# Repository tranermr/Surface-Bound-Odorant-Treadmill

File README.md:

# Surface-Bound-Odorant-Treadmill

One of the important subsets of odors sources used in olfactory navigation is surface-bound sources, which can broadly take the form of point sources or trails. Here, we present an automated treadmill design capable of dynamically printing odor trails of arbitrary lengths and configurations, and with closed-loop control of speed based on the animal’s movement. This design is presented and the utility demonstrated in a corresponding paper studying surface-bound odor trail interactions in locusts (in submission).The uploaded design incorporates some improvements not reflected in the version used in the published paper (i.e. the modification of some components to reduce paper jams, and quality of life improvements). The design is provided in four directories, containing the mechanical components, the electrical component design, and the software and firmware for operation.

The treadmill is designed to enable long-duration interactions with surface-bound odor trails of arbitrary length. Below you can see a video of a locust engaged in a bout of trail following with an odor trail, where the treadmill advances once the locust approaches the front of the behavior chamber, revealing more trail for the locust to interact wtih.

The treadmill is comprised of a series of modules sequentially connected and mounted on an 80-20 frame enabling different slopes to be configured. The design of the mechanical components is provided as an .f3d file, openable using Fusion 360, which is available in [educational](https://www.autodesk.com/campaigns/education/fusion-360-education), or [professional or free versions](https://www.autodesk.com/products/fusion-360/personal/compare).

In the mechanical design file, the design is organized by modules, with the exception of the 'behavior chamber' and 'driver' modules, which are merged in the present design. The organizational structure is arranged to reflect all modules independently for any future revisions. Further details regarding each of the design categories is provided below.

## Mechanical Components
The components of each treadmill module are broken out below. Each module section contains a list of the parts not 3D printed or laser cut from acrylic, as well as suggestions to ease assembly.

### Frame
The treadmill frame is made of 20mm extruded aluminum (2020). The recommended parts list for the frame is

<ins>Misumi</ins>
| Description				| Part Number 		| Quantity|
| ------------- 			|:-------------:	| -----:|
| Aluminum Extrusions 			| HFS5-2020-1500 	| 6 	|
| Aluminum 20mm Brace - optional	| HBLFSNF5-C-SEC 	|   8 	|
| Square Nuts (100 Pack)		| HNKK5-5      		|   2 	|
| Hinges 				| HHPSN5-SET      	|   2 	|

<ins>Grainger</ins>
| Description			| Part Number 		| Quantity|
| ------------- 		|:-------------:	| -----:|
| Bolts M5-0.8 10mm (50 Pack)	| 53GJ15	 	| 5 	|

<ins>Amazon</ins>
| Description			| Part Number 		| Quantity|
| ------------- 		|:-------------:	| -----:|
| Aluminum 20mm Brace (20 Pack)	| [20mm m5 compatible](https://a.co/d/7hRMjW2)	| 3 	|

If cutting yourself, a chopsaw and an aluminum cutting blade (e.g. [Tomax aluminum blade](https://a.co/d/3ZllS9o)) will will greatly ease making accurate and fast cuts compared to a hacksaw.

The HBLFSNF5 braces are optional because while they were used to mount the acrylic components of the evaporation tunnel to the aluminum frame, it is just as practical to mount to the alumium extrusion directly. They are included as an option, but are not suggested.

### Paper Towel Dispenser
The paper towel dispenser is constructed of two vertical mounting bars. The paper towel is hung between the bars on a 1/4" threaded rod, with tension applied to the side of the mount using a compressed spring adjustable via a pair of wingnuts. The position of the two bars (and thereby the alignment of the paper towel with the rig) can be adjusted by advancing or retracting one side or the other using the adjustment screws on the sides. 

<ins>Amazon</ins>
| Description			| Part Number 		| Quantity|
| ------------- 		|:-------------:	| -----:|
| MGN12H 300mm linear rail guide| [MGN12H Rail](https://a.co/d/gDsAsOn)	| 2 	|
| MGN12H Carriage Block		| [MGN12H Carriage Block(https://a.co/d/gDsAsOn)	| 4 	|
| Spring Set			| [SP 9702](https://a.co/d/3PLaYax)	| 1 	|
| Bearing set			| [6202-2RS](https://a.co/d/721F6t8)	| 4 	|

<ins>Hardware Store (or Amazon, etc.)</ins>
| Description			| Part Number 		| Quantity|
| ------------- 		|:-------------:	| -----:|
| 1/4" Threaded Rod 1 foot long	| na			| 3 	|
| 1/4" Nuts			| na			| 20 	|
| 1/4" Wingnuts			| na			| 3 	|

<ins>Grainger</ins>
| Description			| Part Number 		| Quantity|
| ------------- 		|:-------------:	| -----:|
| 1/4" Fender Washers		| 35YU76		| 2 	|

<ins>Assembly of left, right alignment adjustments.</ins>
In the following assembly guides 3D printed components are placed in quotes and referred to by their body names in the Fusion 360 file.

The alignment assemblies consist of a 1' threaded rod, with the following parts threaded on in sequence, pictured below: 
 - Assembly 1: hex nut - "AlignmentScrewInner" - 6202 bearing - "AlignmentScrewInner" - hex nut 
 - Assembly 2: hex nut - spring - hex nut 
 - Assembly 3: hex nut - "AlignmentScrewInner" - 6202 bearing - "AlignmentScrewInner" - hex nut 
 - Assembly 4: hex nut - wing nut

Assemblies 1 and 3 hold the threaded rod and allow rotation.
Assembly 2 is clamped by the "AlignmentBoltClamp" that moves the vertical mounting bar forward or backwards as the threaded rod is rotated. The spring compressed between the two bolts serves to prevent backlash and reduce wobble in the assembly; this is pictured below.
Assembly 4 provides an easy way to rotate the threaded rod, by locking the wing nut in place using the hex nut.

<ins>Assembly of paper towel suspension rod.</ins>
The alignment assemblies consist of a 1' threaded rod, with the following parts threaded on in sequence, pictured below: 
 - Assembly 1: wing nut - "PaperTowelHolderBrace" - hex nut 
 - Assembly 2: hex nut - "PaperTowelInsertInner" - hex nut 
 - Assembly 3: hex nut - hex nut - "PaperTowelInsertInner" - fender washer - spring - fender washer - hex nut - hex nut
 - Assembly 4: hex nut - "PaperTowelHolderBrace" - hex nut 

Assembly 1 holds the threaded rod, but allows the brace to be removed for changing the paper towel roll.
Assembly 2 holds the inner insert for the bearing on which the paper towel pivots.
Assembly 3 holds the inner insert for the second bearing on which the paper towel pivots. In addition, the fender washer compressed against the "TowelInsertOuter" provides friction which tensions the paper towel. By adjusting compression on the spring (or switching to a different spring) the paper towel tension can be tuned to keep the paper towel taut, but minimally burden the driver motor.
Assembly 4 holds the threaded rod.

### Print Carriage Assembly
The print assembly is centered around the print carriage assembly removed from an HP Photosmart C6180 inkjet printer. The inkjet printing assembly is removed, and the "PrintCarriageInsert" is inserted in its place. 

The linear encoder from the print carriage PCB is accessed by connecting to the quadrature encoder using the ribbon cable. This was achieved by producing a breakout board on a piece of FR-4 Copper Clad board, soldering on a compatible ribbon cable mount, and soldering on male 2.54 header pins (pictured below). However, soldering wires directly instead of the pins would reduce risk of accidental disconnection. The traces on the print carriage PCB can also be soldered to directly to avoid needing to construct an adapter. 

<ins>Amazon</ins>
| Description			| Part Number 								| Quantity|
| ------------- 		|:-------------:							| -----:|
| Copper-Clad Board		| [FR-4](https://a.co/d/aHfhtKA)					| 1 	|

<ins>Digikey</ins>
| Description		| Part Number 				| Quantity|
| ------------- 	|:-------------:			| -----:|
| Ribbon Cable Mount	| 18 Pin Flex PCB Mount			| 1 	|

### Print System Assembly
The pressurized print system is comprised of four parts connected in sequence:
 - Air pressure regulator 
 - Print solution reservoir
 - Solenoid valve
 - Printhead

<ins>Printhead assembly</ins>
The printhead construction is the most challenging to fabricate. A 15mm segment is cut from the nylon rod, and drilled using a 6mm bit. One end is tapped to M6 to accomodate the brass printhead, and the other is drilled with a 1/4" bit and tapped to 1/4"-28 to accomodate the adapter for the 1/8" tubing. The printhead threads are wrapped with PTFE tape, and screwed into the nylon segment, taking care that excess PTFE tape is removed prior to insertion. 

Note: If a lathe is available it will greatly ease accurate drilling of the hole, and cutting of the segments. 

Note 2: If the holes are centered (e.g. drilled on a lathe), multiple printheads can be made to ease cleaning and clearing of any clogs that may occur.

<ins>Full assembly</ins>
The regulator is assembled by connecting 1/4" push connect fittings into the inlet and outlet ports. The inlet port is connected to a pressurized air system, and the outlet is connected to the 1/4" tubing. A length of 1/8" Kynar Flex tubing is coated with superglue, and rapidly inserted 5-10cm into the 1/4" tubing, and allowed to dry. The 1/8" tubing is then connected to the Odor Reservoir Cap, and secured in place using the 1/4"-28 adapter with the tubing protruding just inside the cap. A second length of tubing is inserted to the bottom of the flask and similarly secured. The other end of the second length of tubing is then inserted into the inlet port of the Clippard solenoid valve and secured. The outlet port of the solenoid is connected to a third length of tubing, sufficient to run from the position of the solenoid to the print carriage at all points of travel. This will depend on the location where the solenoid is mounted. The third length of tubing is then connected to the printhead using the same 1/4"-28 adapters, and the printhead is inserted into the print carriage to the depth where it just contacts the surface of the paper towel.

<ins>Clippard</ins>
| Description		| Part Number 																| Quantity|
| ------------- 	|:-------------:															| -----:|
| Solenoid valve	| [NR3-2-12, Imperial, Vac to 30psi, 2-way NC, In line ports, 1/4-28 UNF port, 12V](https://www.clippard.com/part/NR3-2-12)		| 1	|

<ins>Amazon</ins>
| Description			| Part Number 								| Quantity|
| ------------- 		|:-------------:							| -----:|
| Nylon Rod 			| [Nylon Rod, 1/2" diameter, 1' length](https://a.co/d/fmmiPHx)		| 1	|
| Brass Printhead Set (4)	| [0.1mm x M6 thread](https://a.co/d/aySFkyX)				| 1 	|

<ins>Cole Parmer</ins>
| Description					| Part Number 																| Quantity|
| ------------- 				|:-------------:															| -----:|
| Odor Reservoir Cap				| [EW-12018-03](https://www.coleparmer.com/i/cole-parmer-vaplock-solvent-delivery-cap-two-1-4-28-ports-gl45-1-ea/1201803)		| 1	|
| 1/8" Tubing to 1/4"-28 adapter (10 pack)	| [EW-12020-08](https://www.coleparmer.com/i/cole-parmer-vaplock-fitting-blue-pp-w-yellow-etfe-straight-compression-to-threaded-adapter-1-8-od-x-1-4-28-unf-m-10-pk/1202008)		| 1|

<ins>VWR</ins>
| Description					| Part Number 																| Quantity|
| ------------- 				|:-------------:															| -----:|
|Transfer Tubing, Kynar Flex™ 2750 PVDF, 1/16" ID x 1/8" OD; 50 ft |  [MFLX95100-01](https://us.vwr.com/store/product/39208964/masterflex-transfer-tubing-kynar-flextm-2750-pvdf-avantor) | 1 |

<ins>Grainger</ins>
| Description					| Part Number 																| Quantity|
| ------------- 				|:-------------:															| -----:|
|PVC Tubing 1/4"OD 1/8"ID |  [2LPT1](https://www.grainger.com/product/TYGON-Tubing-Tygon-S3-B-44-3-2LPT1) | 1 |
|PTFE Tape|  [3PDL5](https://www.grainger.com/product/ANTI-SEIZE-TECHNOLOGY-ANTI-SEIZE-TECH-Thread-Sealant-3PDL5) | 1 |

### Evaporation Tunnel
The plexiglass panels of the evaporation tunnel should be cut, the 3D printed components printed, and all assembled according to the .f3d file. The top tube mount should be connected to the exhaust tubing, and routed to an exhaust line. If additional flow is needed the exhaust fan can be used to increase the exhaust flow.

<ins>Amazon</ins>
| Description			| Part Number 					| Quantity|
| ------------- 		|:-------------:				| -----:|
| Exhaust Fan (optional)	| [MGN12H Rail](https://a.co/d/gDsAsOn)		| 1 	|
| Exhaust Tubing 		| [MGN12H Rail](https://a.co/d/gDsAsOn)		| 1 	|

<ins>Hardware Store (or Amazon, etc.)</ins>
| Description			| Part Number 		| Quantity	|
| ------------- 		|:-------------:	| -----:	|
| 1/4" Acrylic Sheet Clear 	| na			| na 		|

### Behavior Chamber
The plexiglass panels should be cut, the 3D printed components printed, and all assembled according to the .f3d file. The top and bottom panels of the behavior chamber are made of glass sheets; the side of the bottom sheet (and optionally the top sheet) should be trimmed to fit the width of the chamber (249mm) (see .f3d file). The top cover panel can be attached to the front of the behavior chamber using two strips of tape, positioned on the edges past the side of the behavior chamber. 

The inner sides of the behavior chamber acrylic sheets can be coated in fluon; this is most easily done by removing them from the behavior chamber, laying them flat on a counter, and applying the fluon using the brush dispenser in the parts list below. Before reapplying, the sides should be thoroughly cleaned using hot soap and water, and allowed to dry.

<ins>Hardware Store (or Amazon, etc.)</ins>
| Description			| Part Number 		| Quantity	|
| ------------- 		|:-------------:	| -----:	|
| 3/32" Glass Sheet (10" x 12")	| [Shape Glass](https://www.homedepot.com/p/10-in-x-12-in-x-0-09375-in-Clear-Glass-91012/300068325)			| 2 		|
| 1/8" Acrylic Sheet White	| na			| na 		|
| 1/4" Acrylic Sheet Clear	| na			| na 		|

<ins>Amazon</ins>
| Description			| Part Number 		| Quantity	|
| ------------- 		|:-------------:	| -----:	|
| Fluon				| [byFormica Fluon Plus](https://a.co/d/d54PUUA) | 1 		|

### Driver
The plexiglass panels should be cut, the 3D printed components printed, and all assembled according to the .f3d file. The driver and guide rod assemblies, as well as the nylon bushings, were removed from the same HP Photosmart C6180 inkjet printer that supplied the print carriage. One repair was made by replacing the motor with a larger 12V motor removed from [this](https://a.co/d/cd3eFye) peristaltic pump assembly. However, a motor such as [this](https://a.co/d/8RF5Nmk) should also be compatible with the mounting bracket, and the wide range of speeds would enable a fine tuning of maximum speed against torque for the driver assembly.

### Camera Assembly
The aluminum extrusion sections should be cut, the 3D printed components printed, and all assembled according to the .f3d file. The logitech webcam base can be mounted using the 1/4" threaded rod and nut, enabling easy positioning above the behavior chamber.

<ins>Amazon</ins>
| Description			| Part Number 					| Quantity|
| ------------- 		|:-------------:				| -----:|
| Logitech C920S		| [C920S](https://a.co/d/djdxm9s)		| 1 	|

<ins>Hardware Store (or Amazon, etc.)</ins>
| Description			| Part Number 		| Quantity|
| ------------- 		|:-------------:	| -----:|
| 1/4" Threaded Rod 1 inch long	| na			| 1 	|
| 1/4" Nuts			| na			| 1	|

### Backlight
The backlight is comprised of a 1/4" thick plexiglass base upon which IR and white LED strips are alternately layed. The LED strips are soldered together such that either the white (visible) or IR (non-visible) backlight can be used. The light diffuser panels should be cut according to the .f3d file, and can be inserted at multiple levels in the diffuser mount, up to a maximum of 6 panels. 1-2 sheets of paper should be layed over the top of diffuser panels to better distribute the illumination.

<ins>Hardware Store (or Amazon, etc.)</ins>
| Description				| Part Number 						| Quantity|
| ------------- 			|:-------------:					| -----:|
| 1/4" Acrylic Sheet Clear		| na							| 1 	|
| IR LED Strip				| [SMD3528 850nm LED Strip](https://a.co/d/do7MLOz)	| 1	|
| White LED Strip			| [SMD5050 White LED Strip](https://a.co/d/cHSYJyx)	| 1	|
| Light Diffuser Sheet			| [Diffuser](https://www.homedepot.com/p/OPTIX-23-75-in-x-47-75-in-Clear-Plastic-Acrylic-Prismatic-Ceiling-Light-Panel-1A20083A/100550880)	| na	|
| White Printer Paper (8.5"x14")	| [Paper](https://a.co/d/dwqtg2p)			| 1	|

<ins>Grainger</ins>
| Description			| Part Number 		| Quantity	|
| ------------- 		|:-------------:	| -----:	|
| Bolts M5-0.8 35mm (50 Pack) 	| 53GJ20		| 1 		|

## Electrical Components
The circuit layout and PCB design are provided in the form of a KiCAD project. A parts list is provided below:

<ins>Parts List</ins>
| Description		| Part Number 			| Quantity|
| ------------- 	|:-------------:		| -----:|
| Teensy 3.5			| Teensy 3.5		| 1 	|
| 5V Regulator			| L7805CV Through Hole	| 2 	|
| Optoisolator			| 6N137 Through Hole	| 10 	|
| Hex Inverter			| SN74HC14N Through Hole| 2 	|
| TIP41C Transistor		| Tip41C Through Hole	| 2 	|
| Diode				| 1N4002 Through Hole	| 2 	|
| Filter Capacitor		| 4.7uF Through Hole	| 11 	|
| Limit Switch Bias Resistor 1	| 100 Ohm SMD	 	| 1 	|
| Limit Switch Bias Resistor 2	| 1.2 KOhm SMD	 	| 1 	|
| Optoisolator Filter Cap	| 1uF SMD		| 10 	|
| Optoisolator LED Resistor	| 360 Ohm SMD		| 10 	|
| Optoisolator Bias Resistor	| 1 KOhm SMD		| 10 	|

Note: Only two of the four capacitor slots around the voltage regulator are populated. The extra slots can be used if additional filtering is required.

## Software Components
The software is provided in the form of a python script and an embedded program for the Teensy 3.5. 

### Embedded Firmware
The embedded firmware can be uploaded using the [Arduino IDE](https://www.arduino.cc/en/software). 

### Python Software Script
The python software script contains several values that must be configured on the experimental computer in order for communication with the microcontroller (and thereby control over the treadmill) to be achieved. Namely, the serial port and camera input must be specified correctly. To do this 

cap = cv2.VideoCapture(0) in camMain can be set to different camera inputs by changing the '0' to a different number corresponding to the desired input.

ser = serial.Serial('COM4', 2000000, writeTimeout=0) in serMain can be configured to read from a different com port, e.g. 'COM3', and should be configured to match the serial port on which the treadmill is connected.

In addition, the threshold for binarizing the image in order to track the locust must be configured by adjusting the threshold value in the calcSpeed function. Note that this will change when switching between visible and IR backlighting. This can be done by modifying the value of '20' in the below code line to a value found to effectively isolate the animal on the treadmill with the given backlight. 

bw = cv2.threshold(gray, 20, 255, cv2.THRESH_BINARY_INV)[1]

If switching between visible and IR conditions, two versions of the above line can be written, and the unused one commented out prior to running the treadmill.

# Considerations for building
If you are considering building this treadmill there are several considerations that you may want to take into account. The first is whether greater flexibility of odorants, or the width and precision of the trail are more important for your purposes. If some odorants that are incompatible with an inkjet cartridge will be used, then the pressurized reservoir system described in the Print System Assembly section will be the most suitable. However, if the odor panel is limited to odorants that would be compatible with a print cardtridge, then repurposing a print cartridge may provide more consistent and smaller trails. Such a method was used by Dr. Venkatesh Murthy to produce odor trails for mice (see odor trails sections in the [DeepLabCut paper](https://www.nature.com/articles/s41593-018-0209-y#Ack1) by Mathis et al.).

Another consideration is whether to use the optical encoder system used here for the treadmill and print carriage positions. While highly precise, stepper motors likely would produce sufficiently accurate positioning, and may be easier to obtain and configure. This is especially useful if considering expanding the treadmill by adding a second printhead or a system for depositing rewards on the trail (see Suggested Directions for Future Modifications and Expansions) given that the Teensy 3.5 only has two hardware quadrature decoders, both of which are already allocated to the belt encoder and print carriage encoders. Furthermore, if hardware quadrature decoding is not required it would also be possible to utilize the faster Teensy 4.x series microcontrollers or other alternatives.

# Suggested Directions for Future Modifications and Expansions
- Second printhead
- Use of an inkjet module for higher precision trails (albeit with a more constrained odor panel)
- Use of stepper motors instead of the PID controlled print carriage assembly.
- Reward depositor or printer (behavior chamber front slot will need to be raised to avoid rewards being scraped off the paper towel before entering the behavior chamber)

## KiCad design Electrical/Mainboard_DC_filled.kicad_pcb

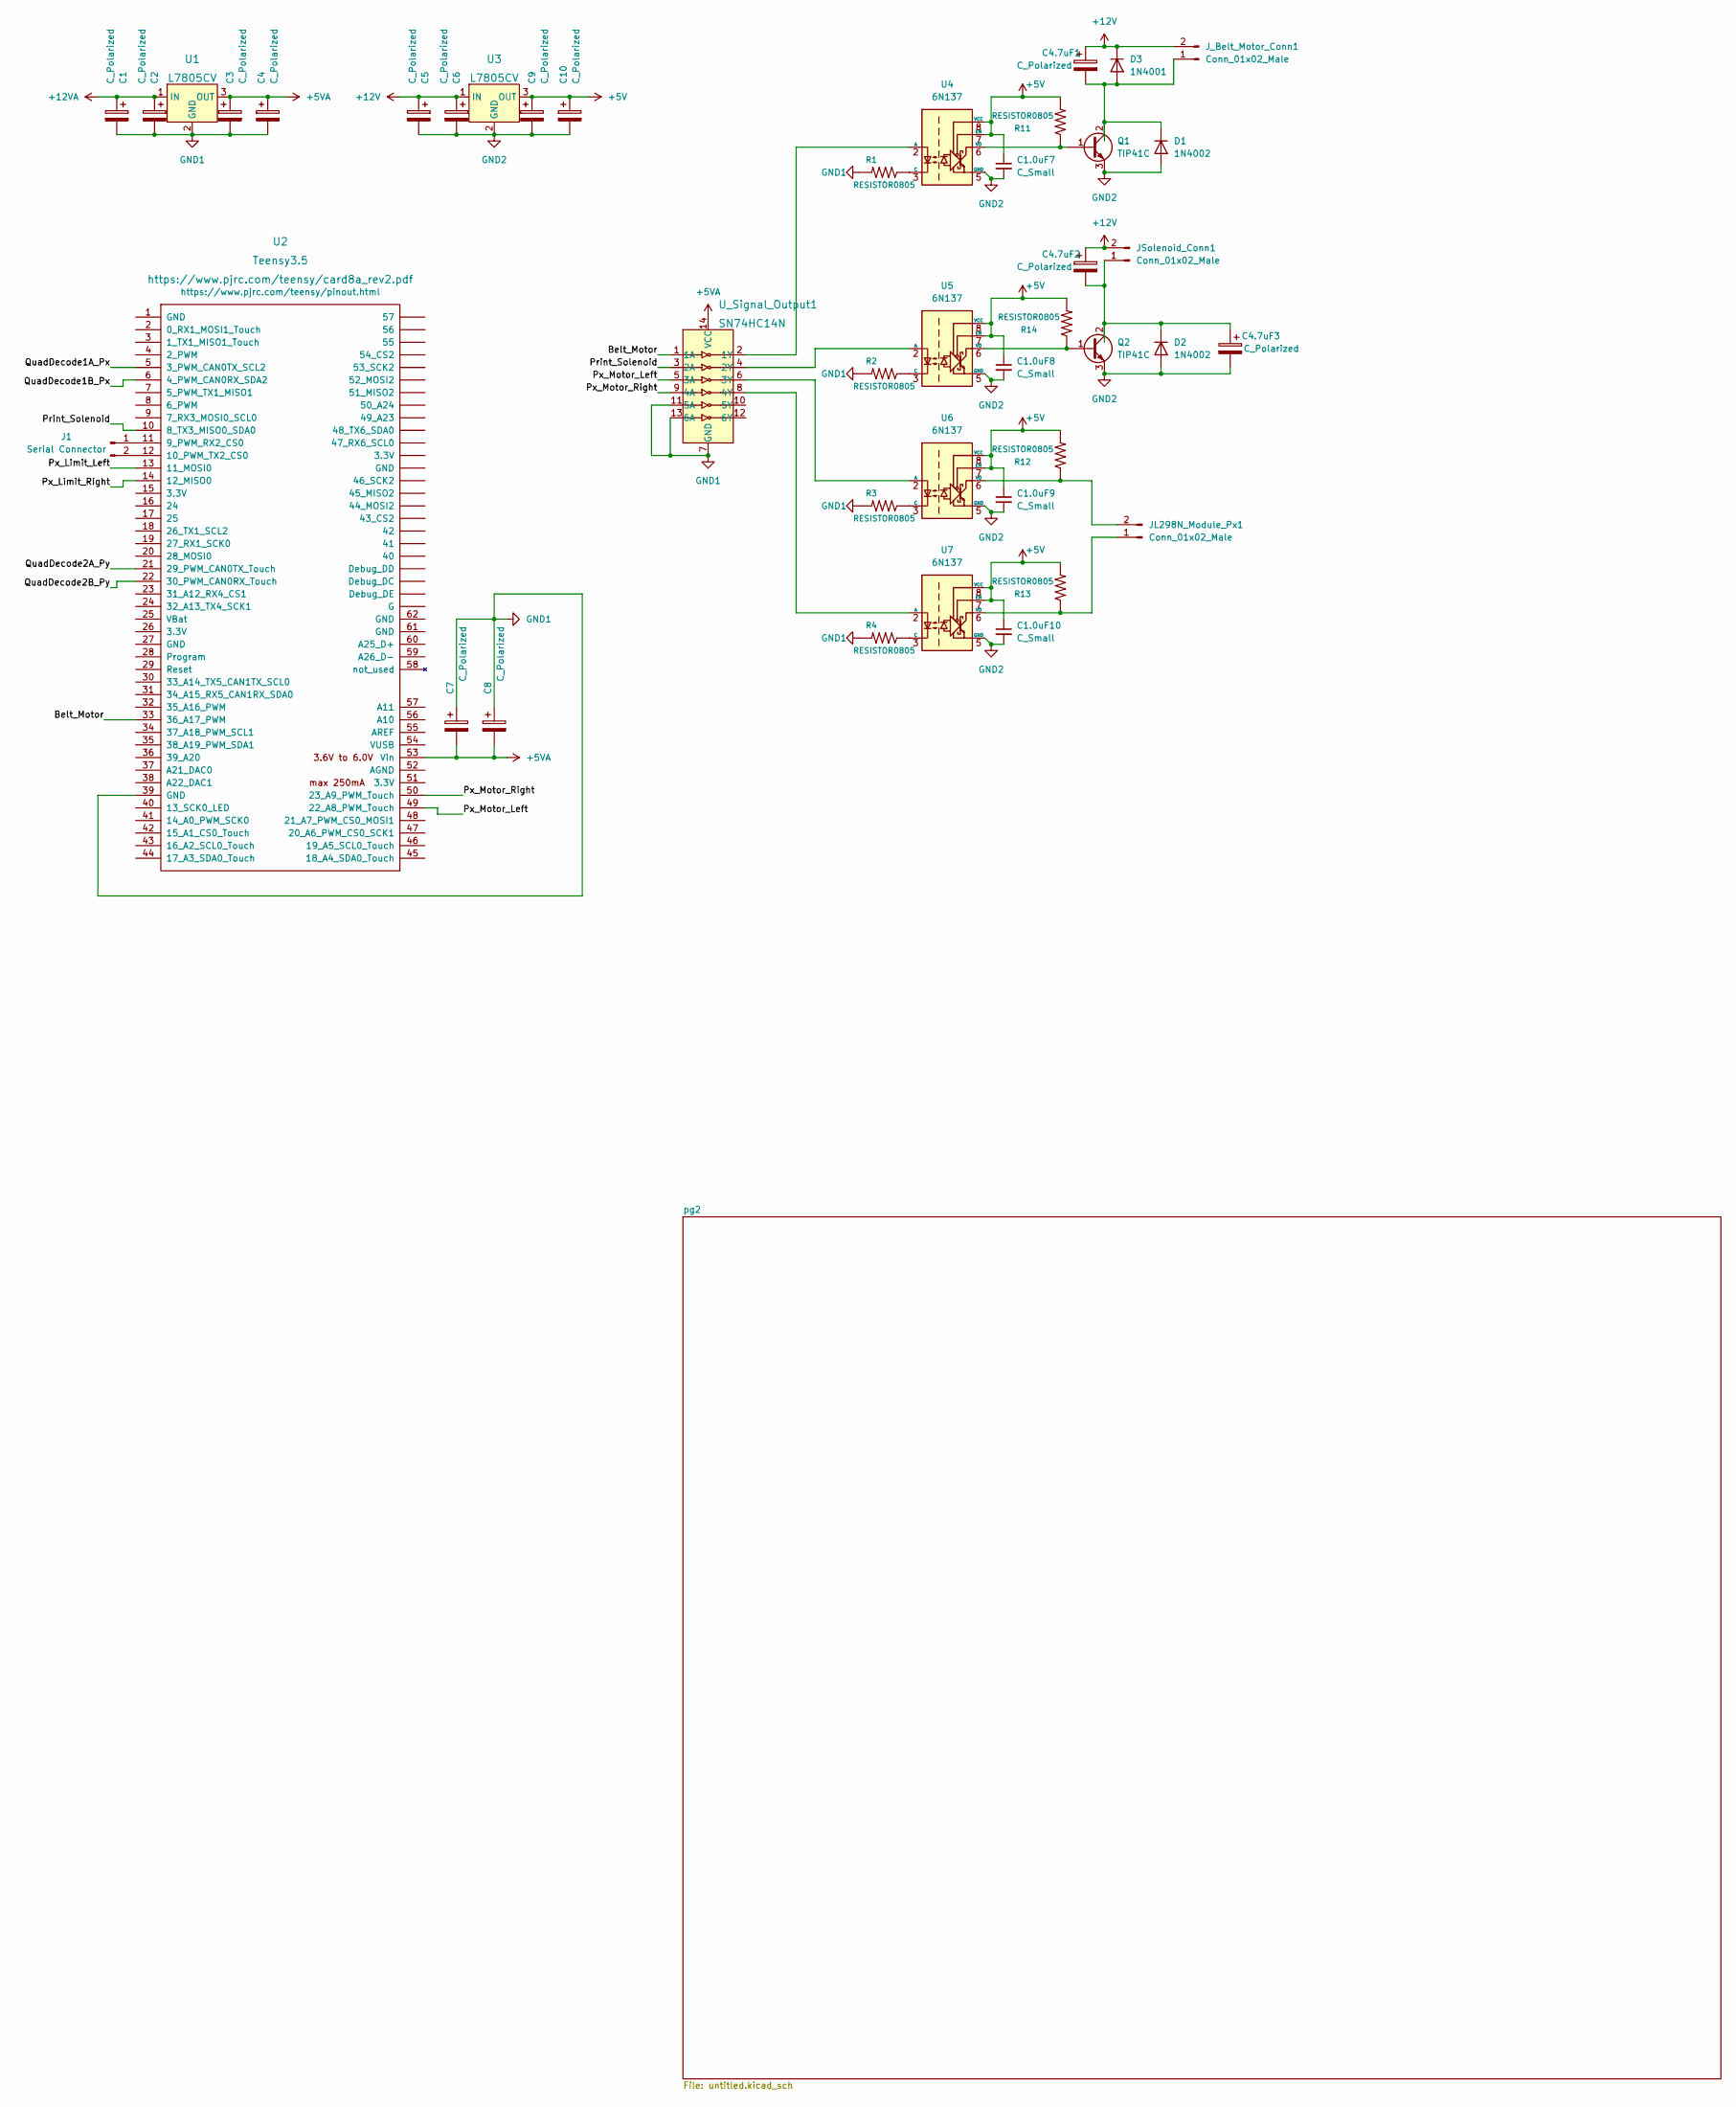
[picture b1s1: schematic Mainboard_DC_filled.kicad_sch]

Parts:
C1, C2, C3, C4, C4.7uF1, C4.7uF2, C4.7uF3, C5, C6, C7, C8, C9, C10: C_Polarized; CP_Radial_D5.0mm_P2.00mm
C1.0uF7, C1.0uF8, C1.0uF9, C1.0uF10: C_Small; C_0805_2012Metric_Pad1.18x1.45mm_HandSolder
D1, D2: 1N4002; D_DO-41_SOD81_P10.16mm_Horizontal
D3: 1N4001; D_DO-41_SOD81_P10.16mm_Horizontal
J1: Serial Connector; PinHeader_1x02_P2.54mm_Vertical
JL298N_Module_Px1: Conn_01x02_Male; PinHeader_1x02_P2.54mm_Vertical
JSolenoid_Conn1: Conn_01x02_Male; PinHeader_1x02_P2.54mm_Vertical
J_Belt_Motor_Conn1: Conn_01x02_Male; PinHeader_1x02_P2.54mm_Vertical
Q1, Q2: TIP41C; TO-220-3_Vertical
R1, R2, R3, R4, R11, R12, R13, R14: RESISTOR0805; R_0805_2012Metric_Pad1.20x1.40mm_HandSolder
U1, U3: L7805CV; TO-220-3; MPN L7805CV; Digi-Key_PN 497-1443-5-ND
U2: Teensy3.5; Teensy35_36
U4, U5, U6, U7: 6N137; DIP-8_W7.62mm
U_Signal_Output1: SN74HC14N; DIP-14_W3mm; MPN SN74HC14N; Digi-Key_PN 296-1577-5-ND

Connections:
+5V: C1.0uF7.1, C1.0uF8.1, C1.0uF9.1, C1.0uF10.1, C9.1, C10.1, R11.2, R12.2, R13.2, R14.2, U3.3 (OUT), U4.7 (EN), U4.8 (VCC), U5.7 (EN), U5.8 (VCC), U6.7 (EN), U6.8 (VCC), U7.7 (EN), U7.8 (VCC); also elsewhere on the board
+5VA: C3.1, C4.1, C7.2, C8.2, U1.3 (OUT), U2.53 (Vin), U_Signal_Output1.14 (VCC); also elsewhere on the board
+12V: C4.7uF1.1, C4.7uF2.1, C5.1, C6.1, D3.1 (K), JSolenoid_Conn1.2, J_Belt_Motor_Conn1.2, U3.1 (IN)
+12VA: C1.1, C2.1, U1.1 (IN)
/Belt_Motor: U2.33 (36_A17_PWM), U_Signal_Output1.1 (1A)
/Print_Solenoid: U2.10 (8_TX3_MISO0_SDA0), U_Signal_Output1.3 (2A)
/Px_Limit_Left: U2.13 (11_MOSI0); also elsewhere on the board
/Px_Limit_Right: U2.14 (12_MISO0); also elsewhere on the board
/Px_Motor_Left: U2.49 (22_A8_PWM_Touch), U_Signal_Output1.5 (3A)
/Px_Motor_Right: U2.50 (23_A9_PWM_Touch), U_Signal_Output1.9 (4A)
/QuadDecode1B_Px: U2.6 (4_PWM_CAN0RX_SDA2); also elsewhere on the board
/QuadDecode2A_Py: U2.21 (29_PWM_CAN0TX_Touch); also elsewhere on the board
/QuadDecode2B_Py: U2.22 (30_PWM_CAN0RX_Touch); also elsewhere on the board
GND1: C1.2, C2.2, C3.2, C4.2, C7.1, C8.1, R1.2, R2.2, R3.2, R4.2, U1.2 (GND), U2.39 (GND), U_Signal_Output1.7 (GND), U_Signal_Output1.11 (5A), U_Signal_Output1.13 (6A); also elsewhere on the board
GND2: C1.0uF7.2, C1.0uF8.2, C1.0uF9.2, C1.0uF10.2, C4.7uF3.2, C5.2, C6.2, C9.2, C10.2, D1.2 (A), D2.2 (A), Q1.3 (E), Q2.3 (E), U3.2 (GND), U4.5 (GND), U5.5 (GND), U6.5 (GND), U7.5 (GND); also elsewhere on the board
unnamed: C4.7uF1.2, D1.1 (K), D3.2 (A), J_Belt_Motor_Conn1.1, Q1.2 (C)
unnamed: C4.7uF2.2, C4.7uF3.1, D2.1 (K), JSolenoid_Conn1.1, Q2.2 (C)
unnamed: J1.1, U2.11 (9_PWM_RX2_CS0)
unnamed: J1.2, U2.12 (10_PWM_TX2_CS0)
unnamed: JL298N_Module_Px1.1, R13.1, U7.6 (VO)
unnamed: JL298N_Module_Px1.2, R12.1, U6.6 (VO)
unnamed: Q1.1 (B), R11.1, U4.6 (VO)
unnamed: Q2.1 (B), R14.1, U5.6 (VO)
unnamed: U4.2 (A), U_Signal_Output1.2 (1Y)
unnamed: R1.1, U4.3 (C)
unnamed: U5.2 (A), U_Signal_Output1.4 (2Y)
unnamed: R2.1, U5.3 (C)
unnamed: U6.2 (A), U_Signal_Output1.6 (3Y)
unnamed: R3.1, U6.3 (C)
unnamed: U7.2 (A), U_Signal_Output1.8 (4Y)
unnamed: R4.1, U7.3 (C)

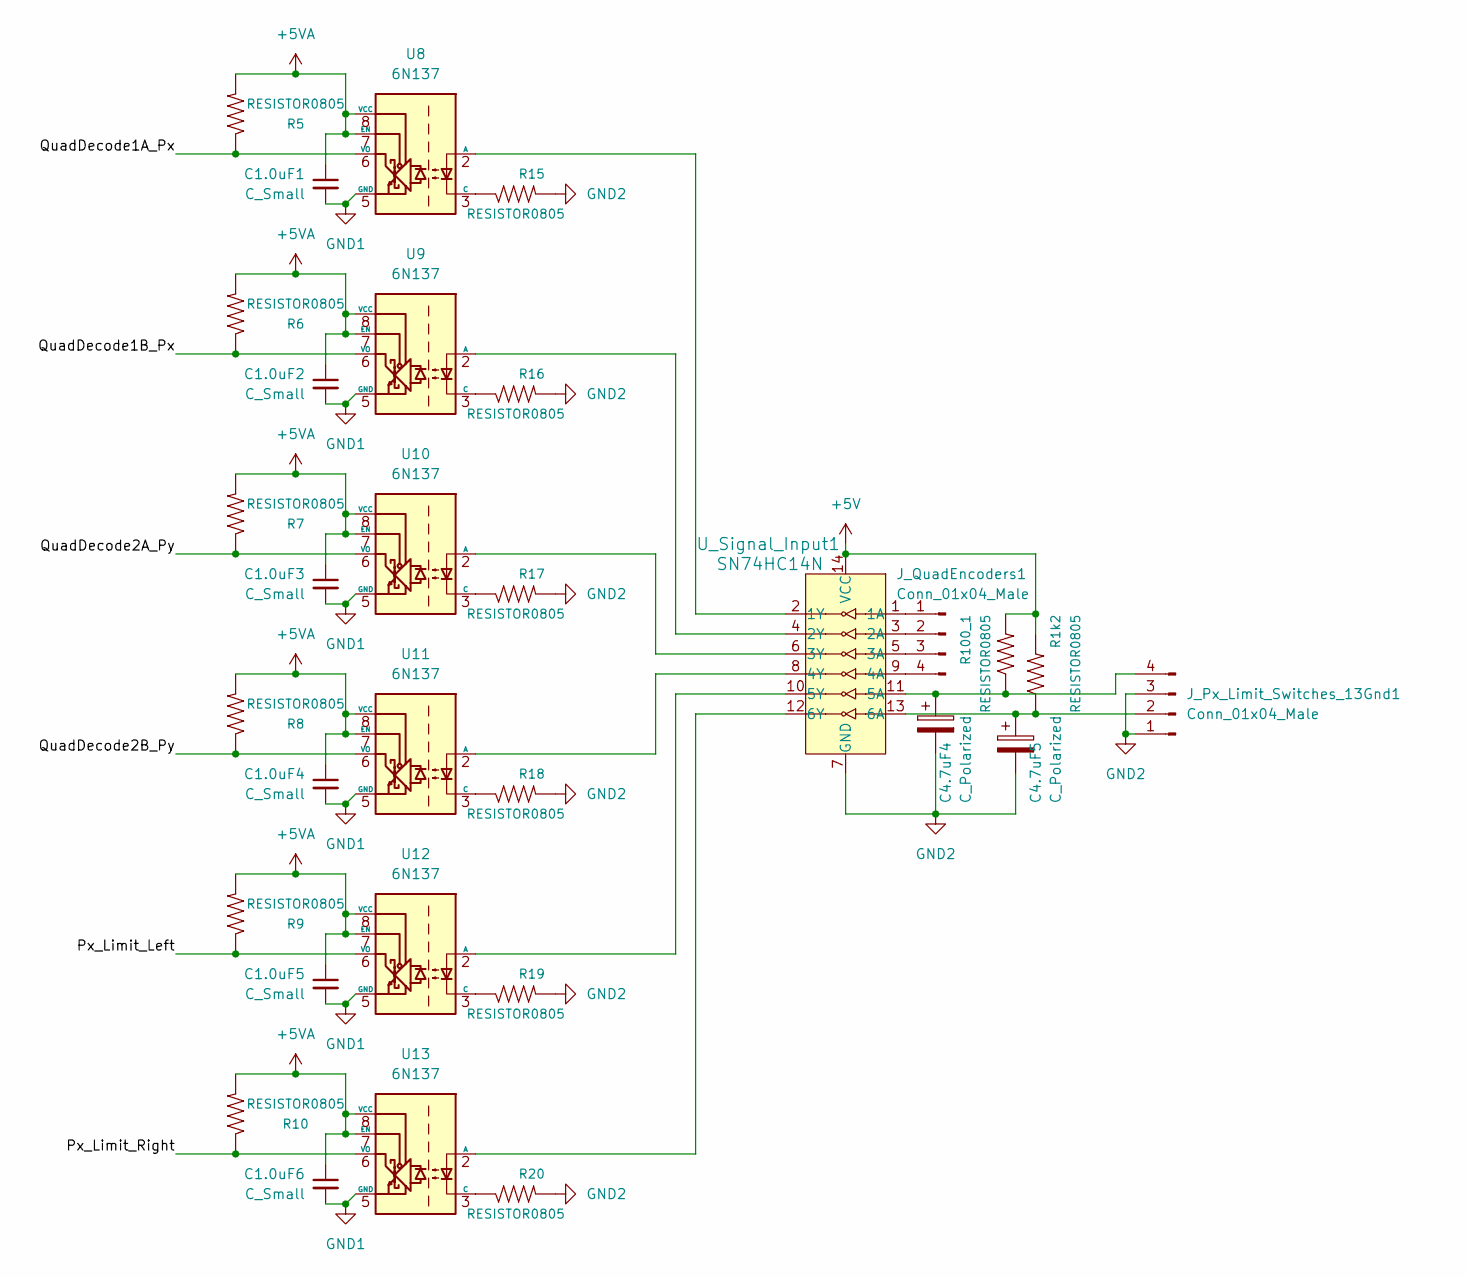
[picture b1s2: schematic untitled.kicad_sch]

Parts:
C1.0uF1, C1.0uF2, C1.0uF3, C1.0uF4, C1.0uF5, C1.0uF6: C_Small; C_0805_2012Metric_Pad1.18x1.45mm_HandSolder
C4.7uF4, C4.7uF5: C_Polarized; CP_Radial_D5.0mm_P2.00mm
J_Px_Limit_Switches_13Gnd1: Conn_01x04_Male; PinHeader_1x04_P2.54mm_Vertical
J_QuadEncoders1: Conn_01x04_Male; PinHeader_1x04_P2.54mm_Vertical
R1k2, R5, R6, R7, R8, R9, R10, R15, R16, R17, R18, R19, R20, R100_1: RESISTOR0805; R_0805_2012Metric_Pad1.20x1.40mm_HandSolder
U8, U9, U10, U11, U12, U13: 6N137; DIP-8_W7.62mm
U_Signal_Input1: SN74HC14N; DIP-14_W3mm; MPN SN74HC14N; Digi-Key_PN 296-1577-5-ND

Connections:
+5V: R1k2.2, R100_1.2, U_Signal_Input1.14 (VCC); also elsewhere on the board
+5VA: C1.0uF1.1, C1.0uF2.1, C1.0uF3.1, C1.0uF4.1, C1.0uF5.1, C1.0uF6.1, R5.2, R6.2, R7.2, R8.2, R9.2, R10.2, U8.7 (EN), U8.8 (VCC), U9.7 (EN), U9.8 (VCC), U10.7 (EN), U10.8 (VCC), U11.7 (EN), U11.8 (VCC), U12.7 (EN), U12.8 (VCC), U13.7 (EN), U13.8 (VCC); also elsewhere on the board
/Px_Limit_Left: R9.1, U12.6 (VO); also elsewhere on the board
/Px_Limit_Right: R10.1, U13.6 (VO); also elsewhere on the board
/QuadDecode1B_Px: R6.1, U9.6 (VO); also elsewhere on the board
/QuadDecode2A_Py: R7.1, U10.6 (VO); also elsewhere on the board
/QuadDecode2B_Py: R8.1, U11.6 (VO); also elsewhere on the board
GND1: C1.0uF1.2, C1.0uF2.2, C1.0uF3.2, C1.0uF4.2, C1.0uF5.2, C1.0uF6.2, U8.5 (GND), U9.5 (GND), U10.5 (GND), U11.5 (GND), U12.5 (GND), U13.5 (GND); also elsewhere on the board
GND2: C4.7uF4.2, C4.7uF5.2, J_Px_Limit_Switches_13Gnd1.1, J_Px_Limit_Switches_13Gnd1.3, R15.2, R16.2, R17.2, R18.2, R19.2, R20.2, U_Signal_Input1.7 (GND); also elsewhere on the board
unnamed: C4.7uF4.1, J_Px_Limit_Switches_13Gnd1.4, R100_1.1, U_Signal_Input1.11 (5A)
unnamed: C4.7uF5.1, J_Px_Limit_Switches_13Gnd1.2, R1k2.1, U_Signal_Input1.13 (6A)
unnamed: J_QuadEncoders1.1, U_Signal_Input1.1 (1A)
unnamed: J_QuadEncoders1.2, U_Signal_Input1.3 (2A)
unnamed: J_QuadEncoders1.3, U_Signal_Input1.5 (3A)
unnamed: J_QuadEncoders1.4, U_Signal_Input1.9 (4A)
unnamed: R16.1, U9.3 (C)
unnamed: R17.1, U10.3 (C)
unnamed: R18.1, U11.3 (C)
unnamed: R19.1, U12.3 (C)
unnamed: R20.1, U13.3 (C)
unnamed: U9.2 (A), U_Signal_Input1.4 (2Y)
unnamed: U10.2 (A), U_Signal_Input1.6 (3Y)
unnamed: U11.2 (A), U_Signal_Input1.8 (4Y)
unnamed: U12.2 (A), U_Signal_Input1.10 (5Y)
unnamed: U13.2 (A), U_Signal_Input1.12 (6Y)

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
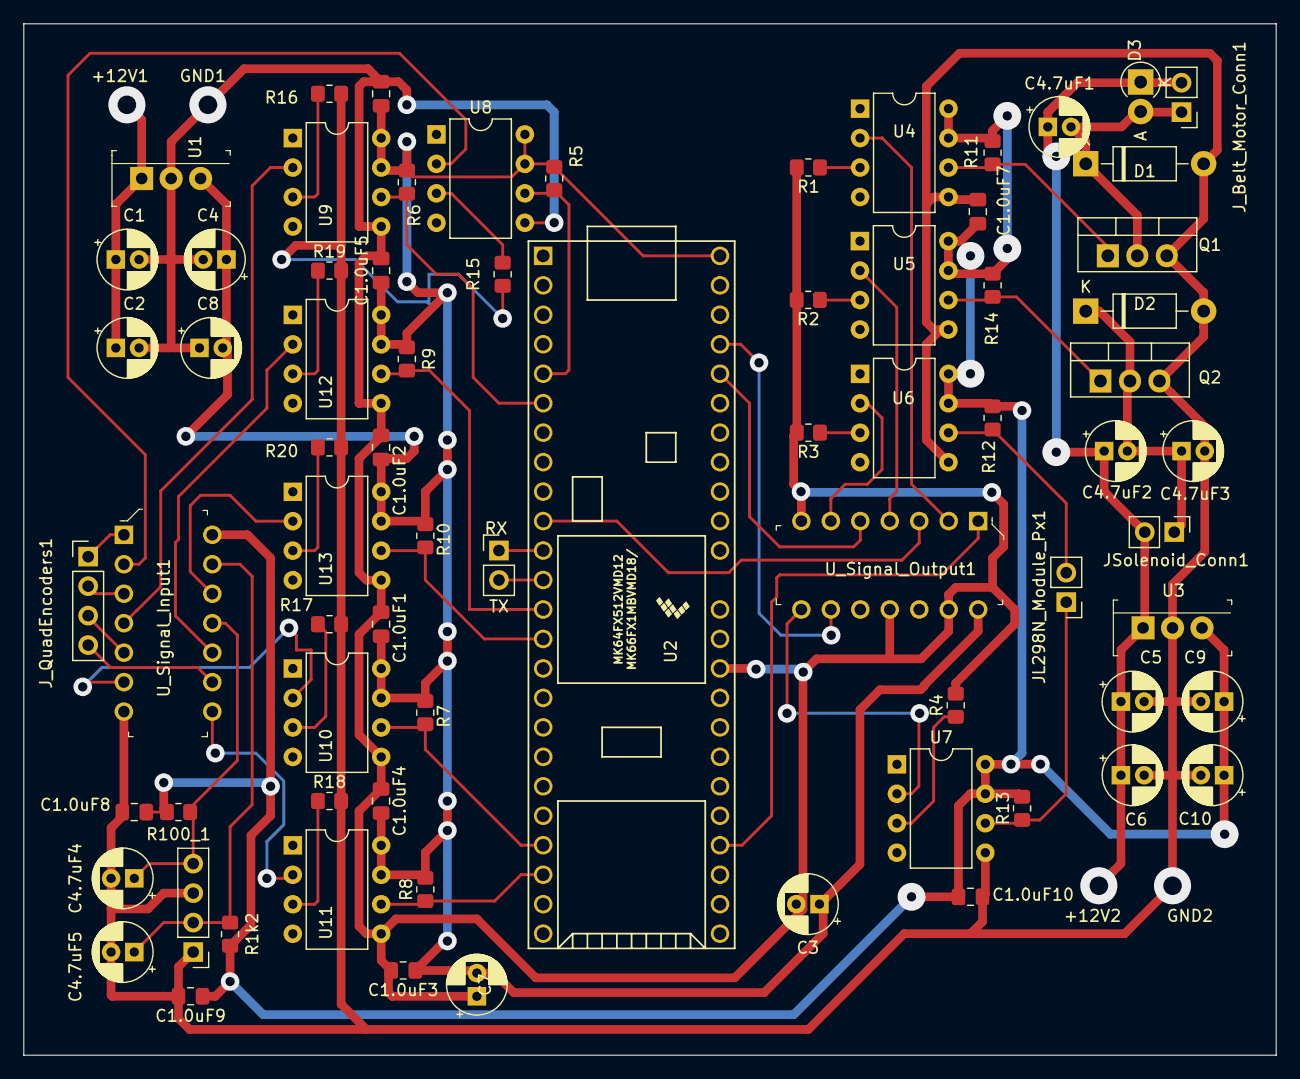
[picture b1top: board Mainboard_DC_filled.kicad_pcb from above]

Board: 2 copper layers, 108.0 x 88.9 mm, 73 parts (0 on the bottom side), 48 nets.

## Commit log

2023-12-14 Added Readme Photo
2023-12-15 Add directory
2023-12-15 Added Electrical, Mechanical Files
2023-12-15 Moved documentation media to dedicated folder
2023-12-15 Updated media folder
2023-12-20 Updated build instructions
2023-12-20 Fixed PCB Error
2023-12-20 Updated readme, added firmware repo and libraries
2023-12-20 Updated readme, reference image
2023-12-20 Updated readme, added python scripts
2023-12-20 Updated readme, cleaned python code
2023-12-20 Updated instructions
    Added print carriage insert reference photos, updated readme
2023-12-20 Cropped photos to improve legibility
2023-12-20 Updated Instructions
